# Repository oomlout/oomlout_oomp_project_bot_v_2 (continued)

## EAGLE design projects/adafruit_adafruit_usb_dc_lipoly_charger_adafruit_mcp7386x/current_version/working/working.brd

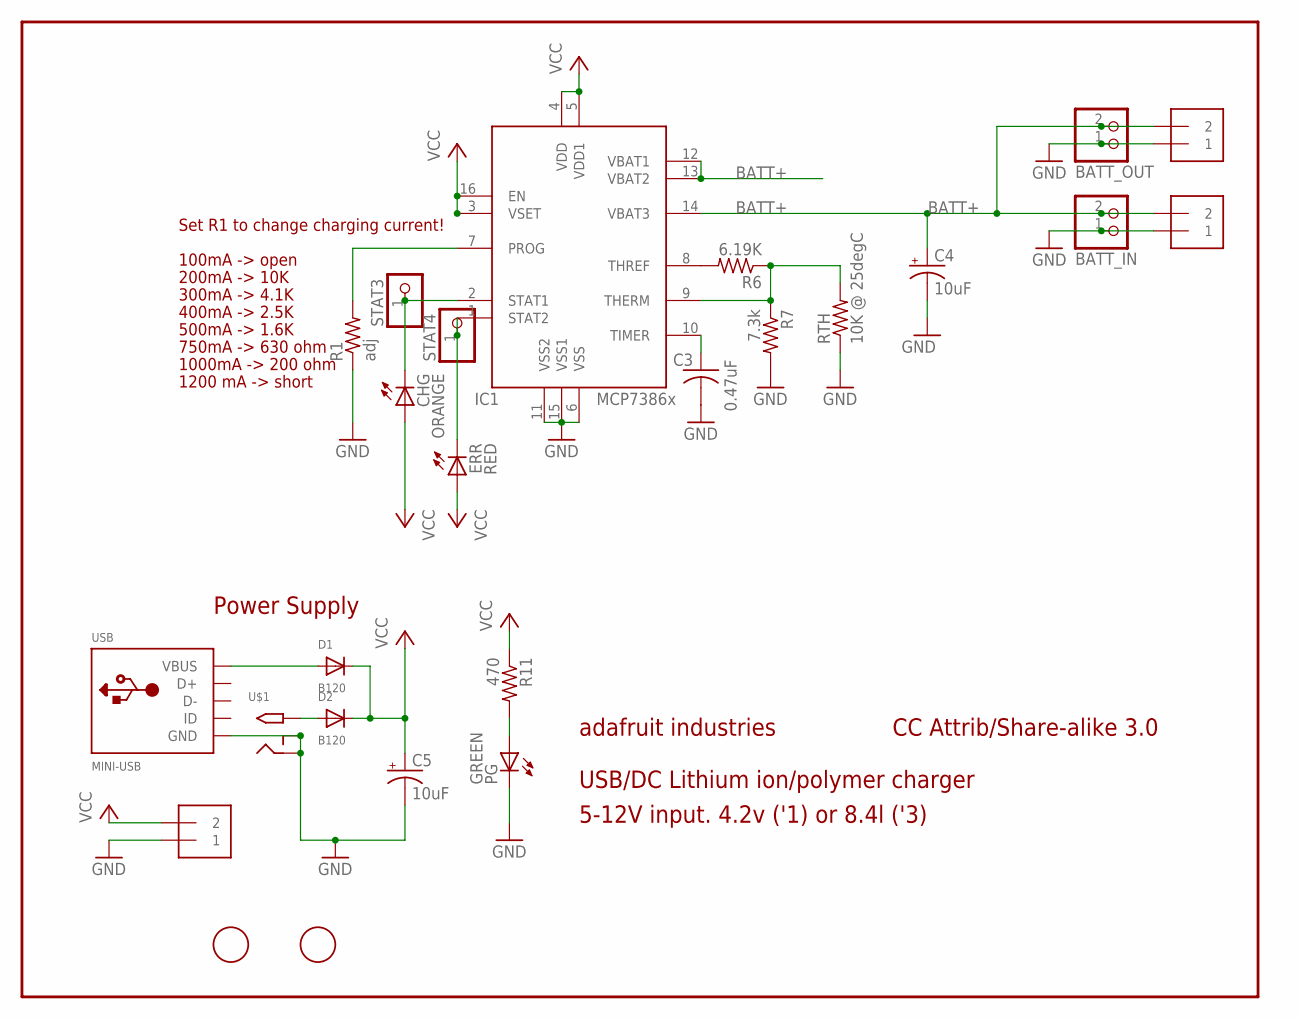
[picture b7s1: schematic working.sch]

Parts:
BATT_IN: JST_2PIN; JSTPH2
BATT_OUT: JST_2PIN; JSTPH2
C3: 0.47uF; C0805K
C4, C5: 10uF; A/3216-18R
CHG: ORANGE; CHIPLED_0805
D1, D2: B120; SMADIODE
ERR: RED; CHIPLED_0805
IC1: MCP7386XS; SO16
IN: 1X2-3.5MM; 3.5MMTERM
OUT: 1X2-3.5MM; 3.5MMTERM
PG: GREEN; CHIPLED_0805
R1: adj; 0805-THM
R6: 6.19K; R0805
R7: 7.3k; R0805
R11: 470; R0805
RTH: 10K @ 25degC; 0805-THM
STAT3, STAT4: PINHD-1X1; 1X01
U$1: 2.1MMJACKSMT; DCJACK_2MM_SMT
U$3, U$4: FIDUCIAL; FIDUCIAL_1MM
USB: MINI-USB; USB-MINIB
VIN: 1X2-3.5MM; 3.5MMTERM

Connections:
BATT+: BATT_IN.2, BATT_OUT.2, C4.+, IC1.12 (VBAT1), IC1.13 (VBAT2), IC1.14 (VBAT3), IN.2, OUT.2
GND: BATT_IN.1, BATT_OUT.1, C3.2, C4.-, C5.-, IC1.6 (VSS), IC1.11 (VSS2), IC1.15 (VSS1), IN.1, OUT.1, PG.C, R1.1, R7.2, RTH.1, U$1.GND (RING), U$1.GNDBREAK (RING_SW), USB.GND, VIN.1
unnamed: D1.A, USB.VBUS
unnamed: IC1.7 (PROG), R1.2
unnamed: CHG.C, IC1.2 (STAT1), STAT3.1
unnamed: ERR.C, IC1.1 (STAT2), STAT4.1
unnamed: C3.1, IC1.10 (TIMER)
unnamed: IC1.8 (THREF), R6.2
unnamed: IC1.9 (THERM), R6.1, R7.1, RTH.2
unnamed: PG.A, R11.2
unnamed: D2.A, U$1.PWR2 (TIP)
VCC: C5.+, CHG.A, D1.C, D2.C, ERR.A, IC1.3 (VSET), IC1.4 (VDD), IC1.5 (VDD1), IC1.16 (EN), R11.1, VIN.2

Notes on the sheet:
Power Supply
Set R1 to change charging current!
200mA -> 10K
300mA -> 4.1K
400mA -> 2.5K
500mA -> 1.6K
750mA -> 630 ohm
1000mA -> 200 ohm
1200 mA -> short
100mA -> open
USB/DC Lithium ion/polymer charger
5-12V input. 4.2v ('1) or 8.4l ('3)
adafruit industries
CC Attrib/Share-alike 3.0

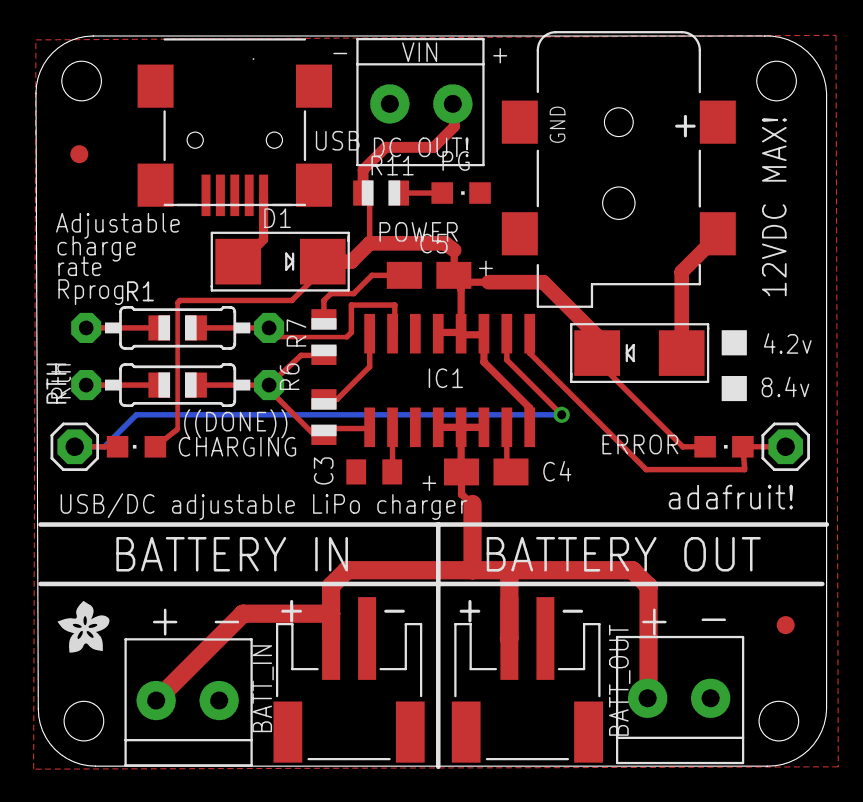
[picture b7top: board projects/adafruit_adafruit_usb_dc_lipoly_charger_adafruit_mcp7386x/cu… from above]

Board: 2 copper layers, 43.9 x 40.6 mm, 26 parts (0 on the bottom side), 12 nets.

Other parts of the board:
U$2: ADAFRUIT200MIL

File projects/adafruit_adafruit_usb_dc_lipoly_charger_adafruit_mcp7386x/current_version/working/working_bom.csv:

"Id";"Designator";"Footprint";"Quantity";"Designation";"Supplier and ref";
1;"C3";"C0805K";1;"0.47uF";;;
2;"D1,D2";"SMADIODE";2;"B120";;;
3;"CHG0";"CHIPLED_0805";1;"ORANGE";;;
4;"U$3,U$4";"FIDUCIAL_1MM";2;"FIDUCIAL";;;
5;"@HOLE3,@HOLE1,@HOLE0,@HOLE2";"";4;"";;;
6;"VIN0,IN0,OUT0";"3.5MMTERM";3;"1X2-3.5MM";;;
7;"BATT_IN0,BATT_OUT0";"JSTPH2";2;"";;;
8;"ERR0";"CHIPLED_0805";1;"RED";;;
9;"R6";"R0805";1;"6.19K";;;
10;"STAT3,STAT4";"1X01";2;"";;;
11;"U$1";"DCJACK_2MM_SMT";1;"2.1MMJACKSMT";;;
12;"C5,C4";"A_3216-18R";2;"10uF";;;
13;"IC1";"SO16";1;"";;;
14;"PG0";"CHIPLED_0805";1;"GREEN";;;
15;"U$2";"ADAFRUIT200MIL";1;"";;;
16;"R7";"R0805";1;"7.3k";;;
17;"R11";"R0805";1;"470";;;
18;"RTH0";"0805-THM";1;"10K @ 25degC";;;
19;"USB0";"USB-MINIB";1;"MINI-USB";;;
20;"R1";"0805-THM";1;"adj";;;

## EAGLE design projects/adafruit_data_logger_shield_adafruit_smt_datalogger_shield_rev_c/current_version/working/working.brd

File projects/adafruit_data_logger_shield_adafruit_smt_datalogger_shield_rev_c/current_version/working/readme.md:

# data_logger_shield
 
## summary 
* id: adafruit_data_logger_shield_adafruit_smt_datalogger_shield_rev_c
* user: adafruit
* name: data_logger_shield
* board: adafruit_smt_datalogger_shield_rev_c
* repo: https://github.com/adafruit/Data-Logger-shield

* src_file_repo_sch: 
* src_file_repo_sch_link: https://github.com/adafruit/Data-Logger-shield/tree/master/
* full details link: https://github.com/oomlout/oomlout_oomp_project_bot_v_2/tree/main/projects/adafruit_data_logger_shield_adafruit_smt_datalogger_shield_rev_c/current_version/working  

## pcb  

[board (pdf)](working.pdf)

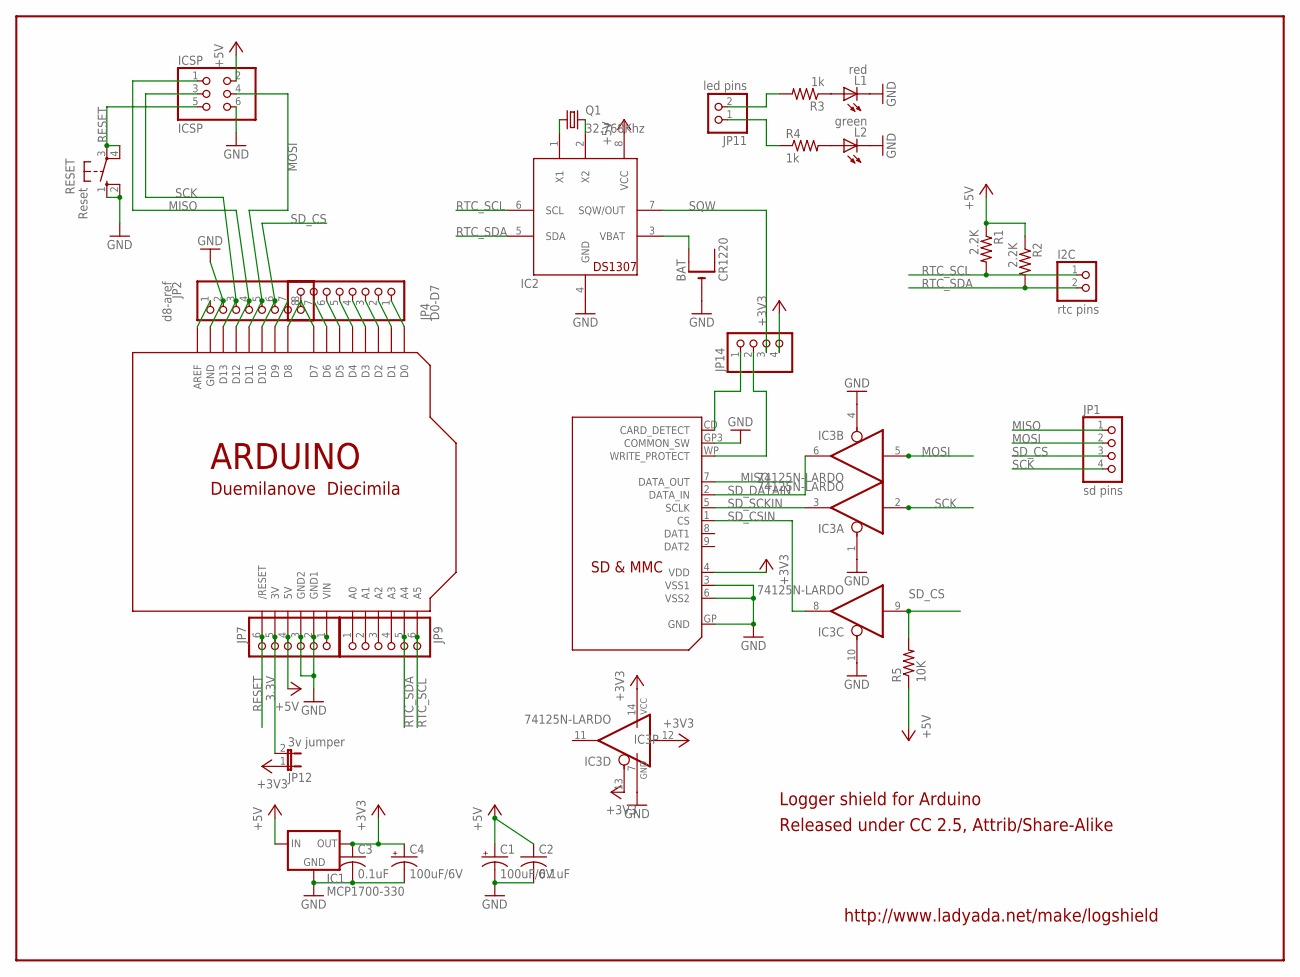
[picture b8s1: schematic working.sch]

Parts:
BAT: CR1220; CR1220-THM
C1, C4: 100uF/6V; E2,5-5
C2, C3: 0.1uF; C025-025X050
I2C: rtc pins; 1X02
IC1: MCP1700-330; TO92
IC2: DS1307; DIL08
IC3: 74125N-LARDO; DIL14-LARDO
ICSP: ICSP; 2X03
JP1: sd pins; 1X04
JP2: d8-aref; 1X08-BIG
JP4: D0-D7; 1X08-BIG
JP7, JP9: PINHD-1X6B; 1X06-BIG
JP11: led pins; 1X02
JP12: 3v jumper; JP1
JP14: PINHD-1X4; 1X04
L1: red; LED3MM
L2: green; LED3MM
Q1: 32.768Khz; TC38H
R1, R2: 2.2K; 0207/10
R3, R4: 1k; 0207/10
R5: 10K; 0207/10
RESET: Reset; B3F-10XX
U$1: ARDUINODUEMILANOVE-NOHOLES; ARDUINO-NOHOLE
U$2: SDMMC06132; 06132

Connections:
3.3V: JP7.5, JP12.2, U$1.3V
+3V3: C3.1, C4.+, IC1.3 (OUT), IC3.12 (I), IC3.13 (OE), IC3.14 (VCC), JP12.1, JP14.4, U$2.4 (VDD)
+5V: C1.+, C2.1, IC1.2 (IN), IC2.8 (VCC), ICSP.2, JP7.4, R1.1, R2.1, R5.1, U$1.5V
GND: BAT.-, C1.-, C2.2, C3.2, C4.-, IC1.1 (GND), IC2.4 (GND), IC3.1 (OE), IC3.4 (OE), IC3.7 (GND), IC3.10 (OE), ICSP.6, JP2.2, JP7.2, JP7.3, L1.K (C), L2.K (C), RESET.1 (S), RESET.2 (S1), U$1.GND, U$1.GND1, U$1.GND2, U$2.3 (VSS1), U$2.6 (VSS2), U$2.GP (GND), U$2.GP3 (COMMON_SW)
MISO: ICSP.1, JP1.1, JP2.4, U$1.D12, U$2.7 (DATA_OUT)
MOSI: IC3.5 (I), ICSP.4, JP1.2, JP2.5, U$1.D11
unnamed: BAT.+1 (+), IC2.3 (VBAT)
unnamed: IC2.1 (X1), Q1.1
unnamed: IC2.2 (X2), Q1.2
unnamed: L1.A, R3.1
unnamed: JP7.1, U$1.VIN
unnamed: JP11.2, R3.2
unnamed: L2.A, R4.2
unnamed: JP11.1, R4.1
unnamed: JP4.1, U$1.D0
unnamed: JP4.2, U$1.D1
unnamed: JP4.3, U$1.D2
unnamed: JP4.4, U$1.D3
unnamed: JP4.5, U$1.D4
unnamed: JP4.6, U$1.D5
unnamed: JP4.7, U$1.D6
unnamed: JP4.8, U$1.D7
unnamed: JP2.1, U$1.AREF
unnamed: JP2.7, U$1.D9
unnamed: JP2.8, U$1.D8
unnamed: JP9.1, U$1.A0
unnamed: JP9.2, U$1.A1
unnamed: JP9.3, U$1.A2
unnamed: JP9.4, U$1.A3
RESET: ICSP.5, JP7.6, RESET.3, RESET.4 (P1), U$1.RESET (/RESET)
RTC_SCL: I2C.1, IC2.6 (SCL), JP9.6, R1.2, U$1.A5
RTC_SDA: I2C.2, IC2.5 (SDA), JP9.5, R2.2, U$1.A4
SCK: IC3.2 (I), ICSP.3, JP1.4, JP2.3, U$1.D13
SD_CD: JP14.1, U$2.CD (CARD_DETECT)
SD_CS: IC3.9 (I), JP1.3, JP2.6, R5.2, U$1.D10
SD_CSIN: IC3.8 (O), U$2.1 (CS)
SD_DATAIN: IC3.6 (O), U$2.2 (DATA_IN)
SD_SCKIN: IC3.3 (O), U$2.5 (SCLK)
SD_WP: JP14.2, U$2.WP (WRITE_PROTECT)
SQW: IC2.7 (SQW/OUT), JP14.3

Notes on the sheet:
http://www.ladyada.net/make/logshield
Released under CC 2.5, Attrib/Share-Alike
Logger shield for Arduino

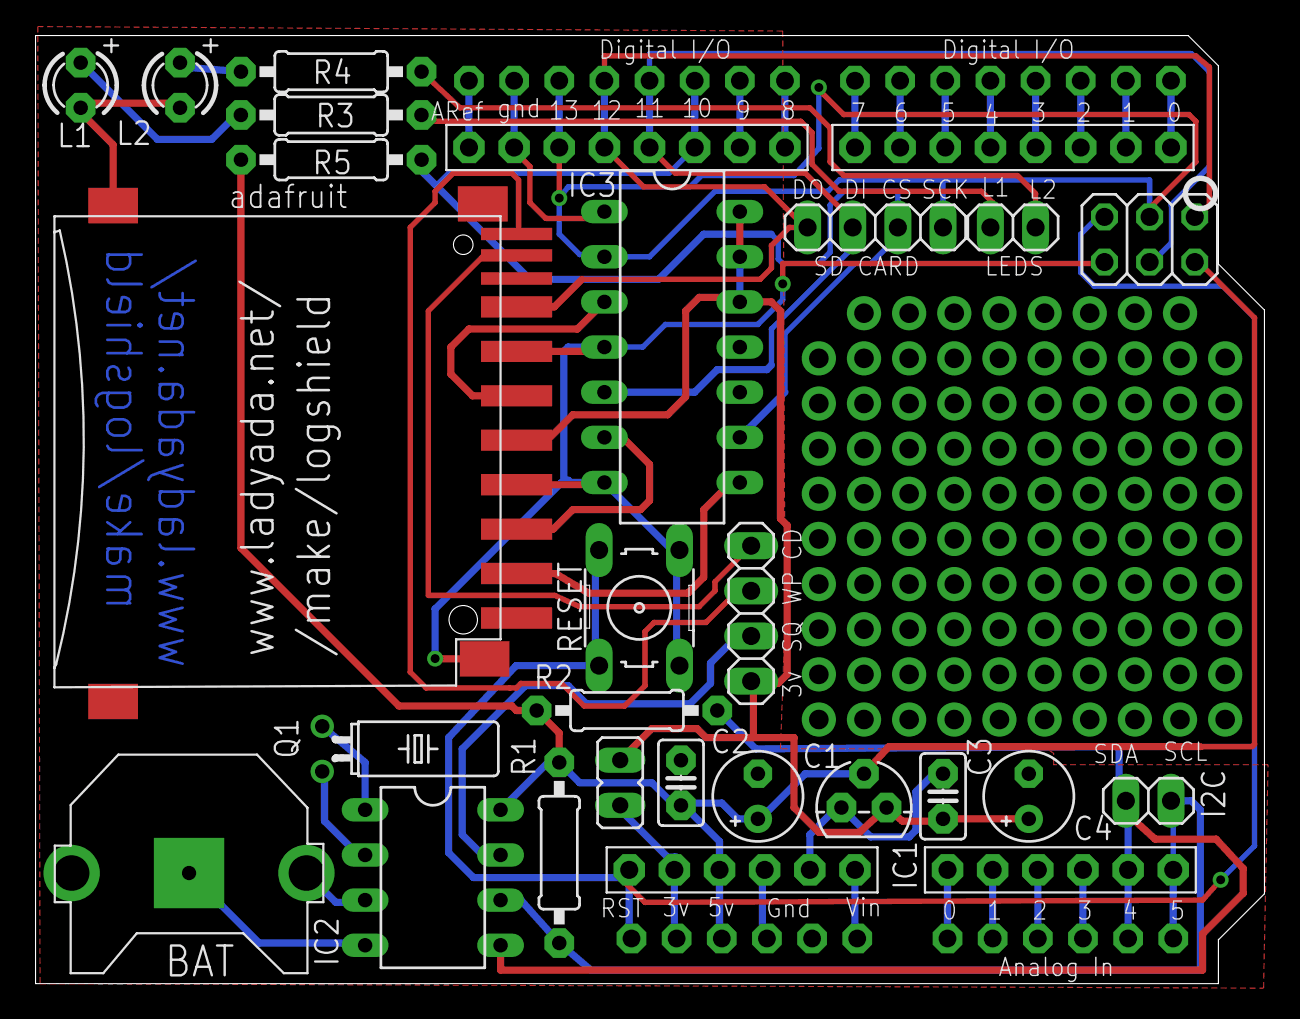
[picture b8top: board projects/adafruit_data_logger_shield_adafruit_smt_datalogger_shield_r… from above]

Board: 2 copper layers, 69.1 x 53.3 mm, 29 parts (0 on the bottom side), 40 nets.
